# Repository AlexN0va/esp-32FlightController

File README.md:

# ESP32-S3 Drone Project 🚁

An ultra-compact, low-cost quadcopter platform powered by the **ESP32-S3 microcontroller**.
This project integrates **wireless control, power management, and a full sensing suite** into a **single PCB design**, achieving a robust and manufacturable drone for under **$50 per unit ($32.01)**.

---

##  Features

### Core Controller

* **ESP32-S3** microcontroller with **WiFi + Bluetooth** for remote control and telemetry.
* **USB-C** interface for programming and charging.
* **Status LEDs** for debugging and state indication.

### 📡 Wireless Control

* Built-in **WiFi/Bluetooth** communication.
* Custom real-time control protocol.

### Power Management

* **350mAh single-cell LiPo battery (1S)**.
* **Integrated charging circuitry** on PCB.
* **TPS5642 buck converter** regulates 3.7–4.2V battery input down to 3.3V.
* **Battery monitoring system** with undervoltage protection for safe operation.

### Motor Control

* **Four brushed DC motors** driven via **low RDS-on MOSFETs**.
* **PWM control** for smooth throttle response.
* Optimized **flyback diode placement** for reduced EMI and motor protection.

### Sensing Suite

* **BMP390 Barometer** – altitude measurements with ±0.5m accuracy.
* **ICM-42670-P 6-axis IMU** – accelerometer + gyroscope.
* **SPI communication** for fast and reliable sensor data exchange.
* **Sensor fusion algorithm** for stabilization.

### Compact Design

* **3.2” x 3.2” arms** with a **central PCB hub**.
* **Single-board design** for simplified manufacturing and assembly.
* **Integrated charging system** – no external circuitry required.

---

## Achieved Milestones

* Full system integration on a **single PCB**.
* Reliable flight stabilization using **sensor fusion**.
* Cost-effective design: **$32.01 BOM cost (under $50 target)**.

---

## Images 

### Final Drone Assembly & PCB Layout & Schematic

https://docs.google.com/presentation/d/1kFseCS2gQPJ-yQV6XV5w5bWRBxy75CzPxFKIJwM_sh4/edit?usp=sharing

---

## 📂 Repository Structure

```bash
├── firmware/          # ESP32-S3 firmware for flight control and wireless comm
├── hardware/          # PCB design files, schematics, layouts
├── docs/              # Images, diagrams, and documentation
└── README.md          # Project overview
```

---

## 🚀 Future Work

* Improve flight algorithms with advanced sensor fusion (Kalman filter / complementary filter).
* Add support for brushless motors + ESCs.
* Expand telemetry features (battery %, orientation, altitude streaming).
* Enhance custom wireless control protocol for lower latency.

---

Would you like me to also **add a wiring diagram block** (using ASCII art or schematic-style markdown) to visually show how the ESP32, sensors, power, and motors connect, so people can understand it even without opening the schematic files?

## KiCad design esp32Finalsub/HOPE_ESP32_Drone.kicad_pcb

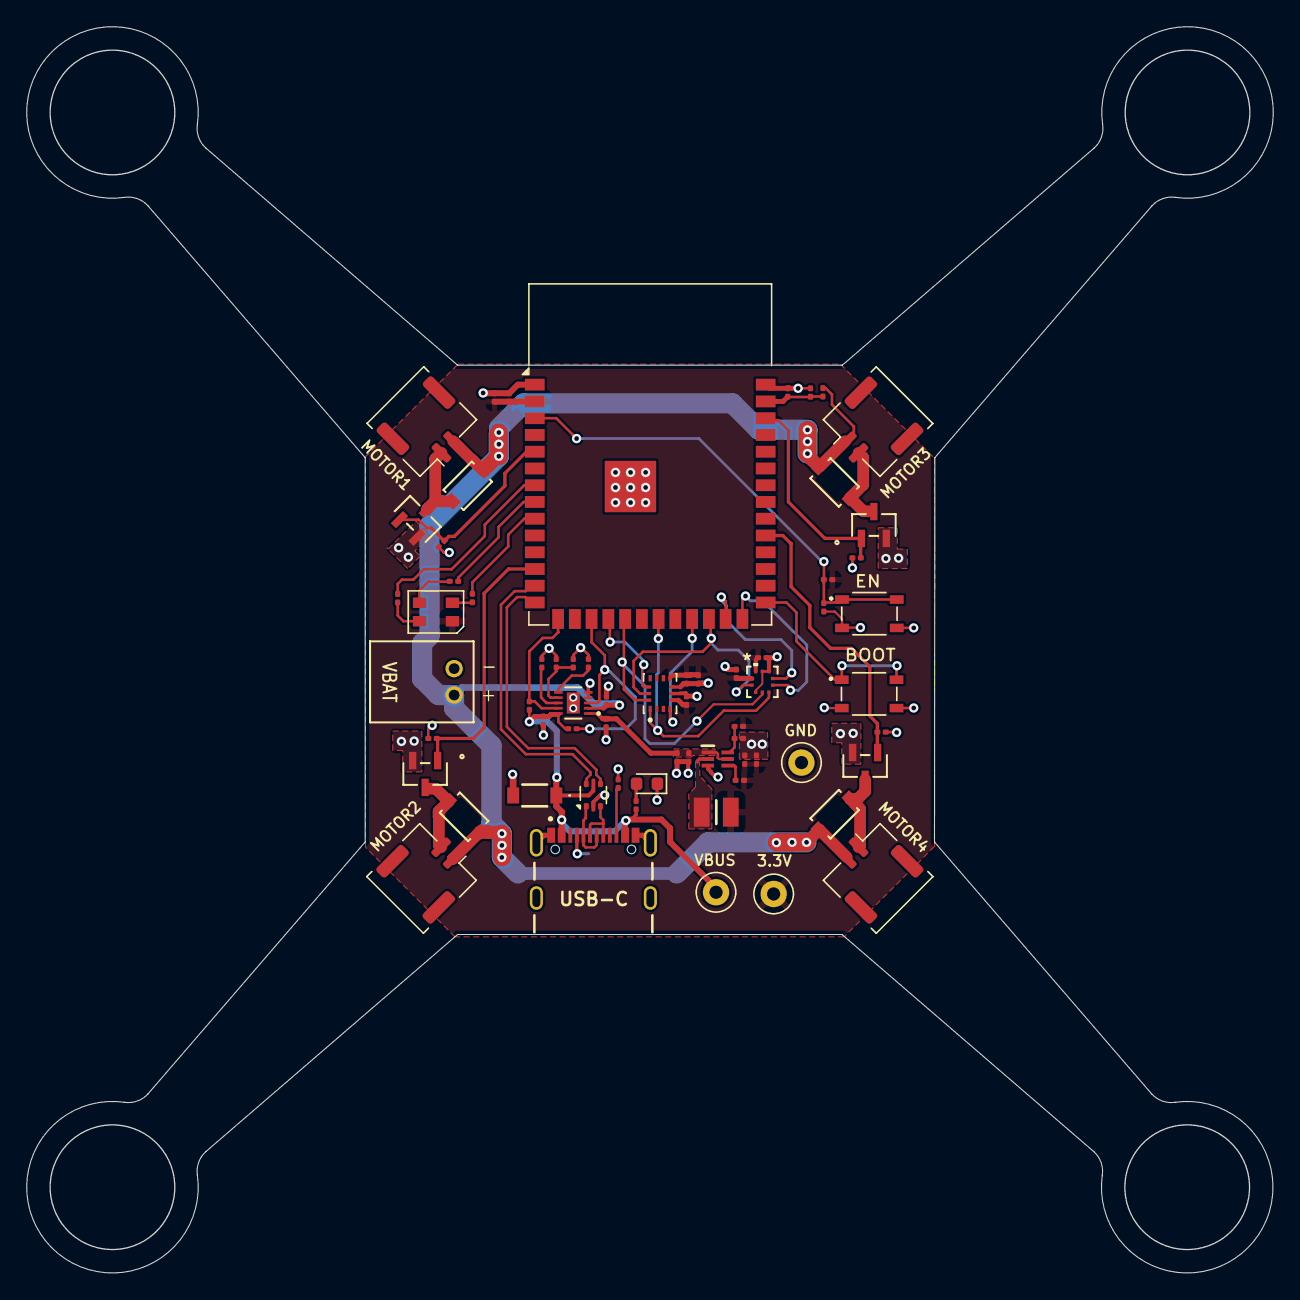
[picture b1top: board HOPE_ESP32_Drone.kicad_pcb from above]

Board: 2 copper layers, 94.4 x 94.4 mm, 67 parts (1 on the bottom side), 44 nets.

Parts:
3.3V: +3.3V; TestPoint_Loop_D1.80mm_Drill1.0mm_Beaded
BOOT: SKRPACE010; SW_SKRPACE010
C4, C6, C7, C25, C31, C32: 0.1uF; C_0201_0603Metric
C5: 22uF; C_0201_0603Metric
C21, C23: 100nF; C_0201_0603Metric
C22, C29: 10uF; C_0201_0603Metric
C24: 10nF; C_0201_0603Metric
C26: 2.2uF; C_0201_0603Metric
C27: 47uF; C_0201_0603Metric
C28, C30: 1uF; C_0201_0603Metric
CR1, CR2, CR3, CR4: PMEG10020ELRX; CFP3_SOD123W_NEX
D1: CLV1L-FKB; LED_Cree-PLCC4_3.2x2.8mm_CCW
D3: SMF5.0AQ-TP; SMF50AQTP
D8: LED; LED_0603_1608Metric
EN: SKRPACE010; SW_SKRPACE010
IC2: TPS564252DRLR; SOT50P160X60-6N
J7: USB4105-GF-A; GCT_USB4105-GF-A
L2: 3.3uH; INDC2520X100N
MOSFET1, MOSFET2, MOSFET3, MOSFET4: SI2302-TP; SOT-23_MCC
MOTOR1: Motor1; Molex_CLIK-Mate_502382-0270_1x02-1MP_P1.25mm_Vertical
MOTOR2: Motor2; Molex_CLIK-Mate_502382-0270_1x02-1MP_P1.25mm_Vertical
MOTOR3: Motor3; Molex_CLIK-Mate_502382-0270_1x02-1MP_P1.25mm_Vertical
MOTOR4: Motor4; Molex_CLIK-Mate_502382-0270_1x02-1MP_P1.25mm_Vertical
MT1: ICM-42670-P; XDCR_ICM-42670-P
R1, R8, R13: 120; R_0201_0603Metric
R2, R6, R7, R9, R10, R11, R12, R19, R21, R22: 10k; R_0201_0603Metric
R3: 100k; R_0201_0603Metric
R4: 50k; R_0201_0603Metric
R5: 220R; R_0201_0603Metric
R20: 45.3k; R_0201_0603Metric
R23: 2k; R_0201_0603Metric
R24: 13k; R_0201_0603Metric
R25: 18k; R_0201_0603Metric
R26, R27: 5k1; R_0201_0603Metric
TP3: GND; TestPoint_Loop_D1.80mm_Drill1.0mm_Beaded
U1: ESP32-S3-WROOM-1
U2: USBLC6-2P6; SOT-666
U4: BQ25185DLHR; WSON10_DLH_TEX
U7: BMP390; 10LGA_2X2X0p75_BOS
VBAT: S2B-PH-K-SLFSN; CONN_S2B-PH-K-S_JST
VBUS: VBUS; TestPoint_Loop_D1.80mm_Drill1.0mm_Beaded

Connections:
+3.3V: 3.3V.1, C5.1, C6.1, C23.1, C24.1, C25.1, C26.1, C27.1, C31.1, C32.1, D1.1 (A), L2.2, MT1.5 (VDDIO), MT1.8 (VDD), R2.1, R19.2, R20.1, U1.2 (3V3), U7.1 (VDDIO), U7.10 (VDD)
+BATT: C28.1, CR1.1, CR2.1, CR3.1, CR4.1, MOTOR1.2, MOTOR2.1, MOTOR3.1, MOTOR4.2, R3.1, U4.2 (BAT), VBAT.2
/BMP_CS: U1.26 (IO45), U7.6 (CSB)
/BMP_INT: U1.25 (IO48), U7.7 (INT)
/D+: J7.A6 (DP1), J7.B6 (DP2), U2.3 (I/O2)
/D-: J7.A7 (DN1), J7.B7 (DN2), U2.1 (I/O1)
/DRIVER1: MOSFET1.1 (G), R9.1, U1.5 (IO5)
/DRIVER2: MOSFET2.1 (G), R10.1, U1.12 (IO8)
/DRIVER3: MOSFET3.1 (G), R11.1, U1.38 (IO2)
/DRIVER4: MOSFET4.1 (G), R12.1, U1.31 (IO38)
/ESP32-S3-WROOM/Boot: BOOT.1, BOOT.2, U1.27 (IO0)
/ESP32-S3-WROOM/EN: C4.1, EN.1, EN.2, R2.2, U1.3 (EN)
/ESP32-S3-WROOM/LED1: R1.1, U1.7 (IO7)
/ESP32-S3-WROOM/LED2: R8.1, U1.8 (IO15)
/ESP32-S3-WROOM/LED3: R13.1, U1.9 (IO16)
/ESP32-S3-WROOM/V_ADC: C7.1, R3.2, R4.1, U1.39 (IO1)
/IMU_CS: MT1.12 (AP_CS), U1.18 (IO10)
/IMU_INT: MT1.4 (INT1/INT), U1.23 (IO21)
/MISO: MT1.1 (AP_SDO/AP_AD0), U1.21 (IO13), U7.5 (SDO)
/MOSI: MT1.14 (AP_SDA/AP_SDIO/AP_SDI), U1.19 (IO11), U7.4 (SDI)
/Motor1-: CR1.2, MOSFET1.3 (D), MOTOR1.1
/Motor2-: CR2.2, MOSFET2.3 (D), MOTOR2.2
/Motor3-: CR4.2, MOSFET3.3 (D), MOTOR3.2
/Motor4-: CR3.2, MOSFET4.3 (D), MOTOR4.1
/REG: C21.1, C22.1, C29.1, IC2.1 (VIN), IC2.5 (EN), U4.1 (SYS)
/SCK: MT1.13 (AP_SCL/AP_SCLK), U1.24 (IO47), U7.2 (SCK)
/STAT1: R6.2, U1.15 (IO3), U4.9 (STAT1)
/STAT2: R7.2, U1.17 (IO9), U4.3 (STAT2)
/SW: IC2.2 (SW), L2.1
/USB+: U1.14 (USB_D+), U2.4 (I/O2)
/USB-: U1.13 (USB_D-), U2.6 (I/O1)
GND: BOOT.3, BOOT.4, C4.2, C5.2, C6.2, C7.2, C21.2, C22.2, C23.2, C24.2, C25.2, C26.2, C27.2, C28.2, C29.2, C30.2, C31.2, C32.2, D3.2 (A), D8.1 (K), EN.3, EN.4, IC2.3 (GND), J7.A1_B12 (GND), J7.B1_A12 (GND), J7.SH1 (SHELL_GND), J7.SH2 (SHELL_GND), J7.SH3 (SHELL_GND), J7.SH4 (SHELL_GND), MOSFET1.2 (S), MOSFET2.2 (S), MOSFET3.2 (S), MOSFET4.2 (S), MT1.6 (GND), MT1.7 (FSYNC), R4.2, R9.2, R10.2, R11.2, R12.2, R21.2, R22.2, R23.2, R24.2, R25.2, R26.2, R27.2, TP3.1, U1.1 (GND), U1.40 (GND), U1.41 (GND), U2.2 (GND), U4.4 (/CE), U4.5 (GND), U4.11 (EPAD), U7.3 (VSS), U7.8 (VSS), U7.9 (VSS), VBAT.1
unnamed: D1.4 (BK), R1.2
unnamed: D1.3 (GK), R8.2
unnamed: D1.2 (RK), R13.2
unnamed: D8.2 (A), R5.2
unnamed: IC2.6 (FB), R20.2, R21.1
unnamed: IC2.4 (PG), R19.1
unnamed: J7.A5 (CC1), R26.1
unnamed: J7.B5 (CC2), R27.1
unnamed: R24.1, R25.1, U4.7 (ILIM/VSET)
unnamed: R23.1, U4.8 (ISET)
unnamed: R22.1, U4.6 (TS/MR)
VBUS: C30.1, D3.1 (K), J7.A4_B9 (VBUS), J7.B4_A9 (VBUS), R5.1, R6.1, R7.1, U2.5 (VBUS), U4.10 (IN), VBUS.1

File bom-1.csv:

Designator,Footprint,Quantity,Value,LCSC Part #
3.3V,TestPoint_Loop_D1.80mm_Drill1.0mm_Beaded,1,+3.3V,
"BOOT, EN",SW_SKRPACE010,2,SKRPACE010,
"C21, C23",0201,2,100nF,
"C22, C29",0201,2,10uF,
C24,0201,1,10nF,
"C25, C31, C32, C4, C6, C7",0201,6,0.1uF,
C26,0201,1,2.2uF,
C27,0201,1,47uF,
"C28, C30",0201,2,1uF,
C5,0201,1,22uF,
"CR1, CR2, CR3, CR4",CFP3_SOD123W_NEX,4,PMEG10020ELRX,
D1,LED_Cree-PLCC4_3.2x2.8mm_CCW,1,CLV1L-FKB,
D3,SMF50AQTP,1,SMF5.0AQ-TP,
D8,0603,1,LED,
IC2,SOT50P160X60-6N,1,TPS564252DRLR,
J7,GCT_USB4105-GF-A,1,USB4105-GF-A,
L2,INDC2520X100N,1,3.3uH,
"MOSFET1, MOSFET2, MOSFET3, MOSFET4",SOT-23_MCC,4,SI2302-TP,
MOTOR1,Molex_CLIK-Mate_502382-0270_1x02-1MP_P1.25mm_Vertical,1,Motor1,
MOTOR2,Molex_CLIK-Mate_502382-0270_1x02-1MP_P1.25mm_Vertical,1,Motor2,
MOTOR3,Molex_CLIK-Mate_502382-0270_1x02-1MP_P1.25mm_Vertical,1,Motor3,
MOTOR4,Molex_CLIK-Mate_502382-0270_1x02-1MP_P1.25mm_Vertical,1,Motor4,
MT1,XDCR_ICM-42670-P,1,ICM-42670-P,
"R1, R13, R8",0201,3,120,
"R10, R11, R12, R19, R2, R21, R22, R6, R7, R9",0201,10,10k,
R20,0201,1,45.3k,
R23,0201,1,2k,
R24,0201,1,13k,
R25,0201,1,18k,
"R26, R27",0201,2,5k1,
R3,0201,1,100k,
R4,0201,1,50k,
R5,0201,1,220R,
TP3,TestPoint_Loop_D1.80mm_Drill1.0mm_Beaded,1,GND,
U1,ESP32-S3-WROOM-1,1,ESP32-S3-WROOM-1,
U2,SOT-666,1,USBLC6-2P6,
U4,WSON10_DLH_TEX,1,BQ25185DLHR,
U7,10LGA_2X2X0p75_BOS,1,BMP390,
VBAT,CONN_S2B-PH-K-S_JST,1,S2B-PH-K-SLFSN,
VBUS,TestPoint_Loop_D1.80mm_Drill1.0mm_Beaded,1,VBUS,
